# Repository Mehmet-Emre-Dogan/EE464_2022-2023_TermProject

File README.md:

# EE464_2022-2023_TermProject
 Hardware Project for EE464

 https://github.com/odtu/ee464

# Magnetic Design Report
 https://github.com/Mehmet-Emre-Dogan/EE464_2023_HW2_Team08
 
 # Experiments
 
 ## 0th Experiment
 https://youtu.be/MJ3PV6YCNdQ

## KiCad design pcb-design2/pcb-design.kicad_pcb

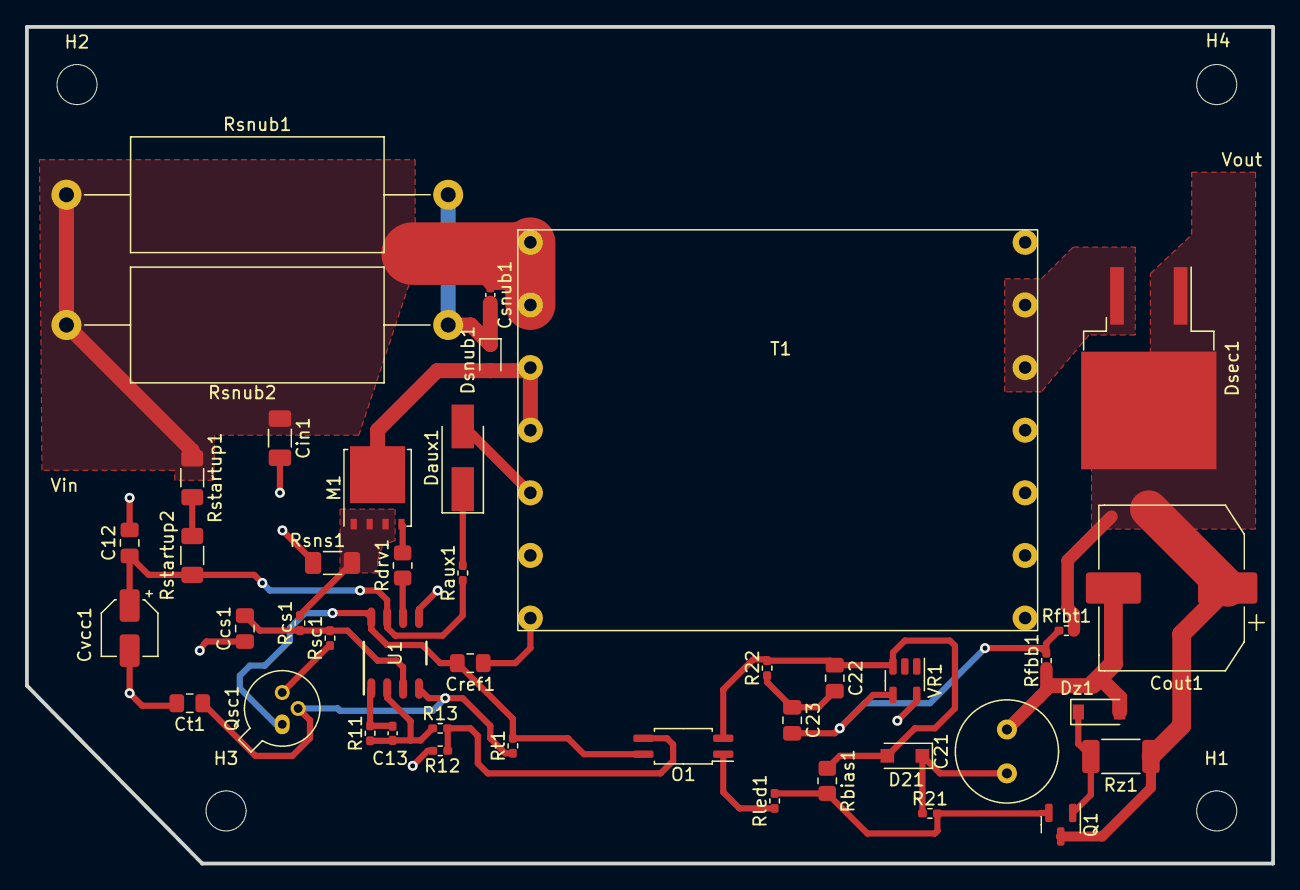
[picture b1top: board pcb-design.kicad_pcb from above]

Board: 2 copper layers, 99.5 x 66.8 mm, 48 parts (0 on the bottom side), 28 nets.

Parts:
C12: 100 nF; C_0805_2012Metric_Pad1.18x1.45mm_HandSolder
C13: 1 nF; C_0402_1005Metric_Pad0.74x0.62mm_HandSolder
C21: 68 uF; C_Radial_D8.0mm_H11.5mm_P3.50mm
C22: 22 pF; C_0805_2012Metric_Pad1.18x1.45mm_HandSolder
C23: 56 pF; C_0805_2012Metric_Pad1.18x1.45mm_HandSolder
Ccs1: 470 pF; C_0805_2012Metric_Pad1.18x1.45mm_HandSolder
Cin1: 4.7 uF; C_1206_3216Metric_Pad1.33x1.80mm_HandSolder
Cout1: 47 uF; CP_Elec_12.5x13
Cref1: 100 nF; C_0805_2012Metric_Pad1.18x1.45mm_HandSolder
Csnub1: 2.2 uF; C_0402_1005Metric_Pad0.74x0.62mm_HandSolder
Ct1: 1 nF; C_0805_2012Metric_Pad1.18x1.45mm_HandSolder
Cvcc1: 4.7 uF; CP_Elec_4x5.3
D21: PMEG6010CEH; D_SOD-123F
Daux1: D_Schottky; D_SMA_Handsoldering
Dsec1: D; TO-263-2_TabPin1
Dsnub1: D_Schottky; D_SOD-323
Dz1: D_Zener; D_SOD-123
H1, H2, H3, H4: MountingHole; MountingHole_3.2mm_M3
M1: CSD19502Q5B; TDSON-8-1
O1: TCMT1107; SOP-4_4.4x2.6mm_P1.27mm
Q1: BC846; SOT-23
Qsc1: 2N2646; TO-18-3
R11, R21: 10 kR; R_0402_1005Metric_Pad0.72x0.64mm_HandSolder
R12: 7.68 kR; R_0402_1005Metric_Pad0.72x0.64mm_HandSolder
R13: 4.99 kR; R_0402_1005Metric_Pad0.72x0.64mm_HandSolder
R22: 1.15 MR; R_0402_1005Metric_Pad0.72x0.64mm_HandSolder
Raux1: 10 R; R_0402_1005Metric_Pad0.72x0.64mm_HandSolder
Rbias1: 13.7 kR; R_0805_2012Metric_Pad1.20x1.40mm_HandSolder
Rcs1: 1 kR; R_0402_1005Metric_Pad0.72x0.64mm_HandSolder
Rdrv1: 12.1 R; R_0805_2012Metric_Pad1.20x1.40mm_HandSolder
Rfbb1: 3.01 kR; R_0402_1005Metric_Pad0.72x0.64mm_HandSolder
Rfbt1: 54.9 kR; R_0402_1005Metric_Pad0.72x0.64mm_HandSolder
Rled1: 16.2 kR; R_0402_1005Metric_Pad0.72x0.64mm_HandSolder
Rsc1: 4.32 kR; R_0402_1005Metric_Pad0.72x0.64mm_HandSolder
Rsns1: 33.9637 mR; R_1206_3216Metric_Pad1.30x1.75mm_HandSolder
Rsnub1, Rsnub2: 118.452 R; R_Axial_DIN0922_L20.0mm_D9.0mm_P30.48mm_Horizontal
Rstartup1, Rstartup2: 3.83 kR; R_1206_3216Metric_Pad1.30x1.75mm_HandSolder
Rt1: 7.5 kR; R_0402_1005Metric_Pad0.72x0.64mm_HandSolder
Rz1: 20 kR; R_2010_5025Metric_Pad1.40x2.65mm_HandSolder
T1: Transformer_1P_2S; Custom_Transformer-P0.5-7
U1: UCC2813D-1; UCC2813-1D
VR1: TL431DBV; SOT-23-5

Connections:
GND: C21.2, Cout1.2, Dz1.2 (A), Rfbb1.1, T1.11, T1.12, VR1.5 (A)
GNDREF: C12.2, Ccs1.1, Cin1.2, Cref1.1, Ct1.2, Cvcc1.2, R12.1, Rsns1.1, T1.6 (SD), T1.7, U1.5 (GND)
unnamed: C12.1, Cvcc1.1, Raux1.1, Rstartup2.2, U1.7 (VCC)
unnamed: C13.1, R11.1, R13.1, U1.2 (FB)
unnamed: C13.2, R11.2, U1.1 (COMP)
unnamed: C21.1, D21.1 (K), R21.1
unnamed: C22.1, D21.2 (A), O1.2, R22.2, Rbias1.1, VR1.3 (K)
unnamed: C22.2, C23.1, R22.1
unnamed: C23.2, Rfbb1.2, Rfbt1.1, VR1.4 (REF)
unnamed: Ccs1.2, Rcs1.1, Rsc1.2, U1.3 (CS)
unnamed: Cref1.2, O1.4, Qsc1.1 (B2), Rt1.2, U1.8 (REF)
unnamed: Csnub1.2, Dsnub1.1 (K), Rsnub1.2, Rsnub2.2
unnamed: Ct1.1, Qsc1.2 (E), Rt1.1, U1.4 (RC)
unnamed: Daux1.1 (K), Raux1.2
unnamed: Daux1.2 (A), T1.5 (SC)
unnamed: Dsec1.2 (A), T1.9, T1.10
unnamed: Dsnub1.2 (A), M1.5 (D), T1.3 (SA), T1.4 (SB)
unnamed: Dz1.1 (K), Q1.1 (B), Rz1.2
unnamed: M1.1 (S), M1.2 (S), M1.3 (S), Rcs1.2, Rsns1.2
unnamed: M1.4 (G), Rdrv1.2
unnamed: O1.1, Rled1.1
unnamed: O1.3, R12.2, R13.2
unnamed: Q1.2 (E), R21.2, Rbias1.2, Rled1.2
unnamed: Qsc1.3 (B1), Rsc1.1
unnamed: Rdrv1.1, U1.6 (OUT)
unnamed: Rstartup1.2, Rstartup2.1
VDC: Cin1.1, Csnub1.1, Rsnub1.1, Rsnub2.1, Rstartup1.1, T1.1 (AA), T1.2 (AB)
Vout: Cout1.1, Dsec1.1 (K), Q1.3 (C), Rfbt1.2, Rz1.1

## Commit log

2023-02-04 worked on fixed duty pwm generator
    used ne555
2023-02-04 added irfz44n to spice sim.
2023-02-05 redesign circuit with existing elements
2023-02-05 add experimental images for the 555 cct
2023-03-12 Create handdrawn_sch.jpeg
    an approach to perform DC isolation
2023-04-02 move files
2023-05-01 transformer winding experiment
2023-05-05 web scraper for part links
2023-05-06 BOM list updated.
2023-05-07 Create presentation.pptx
    - Problem Definition
    - Topology Selection
    - Plan B
    - Targeted Bonuses
2023-05-09 Presentation completed.
2023-05-11 Update README.md
    Add zeroth experiment video link
2023-05-21 copy core calculator mlx from the hw2
2023-05-21 turns calculation with a new core
2023-05-27 add skin depth calculation and
    recalculate the effective AC resistances
2023-06-11 Schematic and footprints added for PCB design.
2023-06-11 Transformer footprint is added.
2023-06-14 Schematic is corrected. PCB Design is added.
2023-06-14 Case design is added and some minor fixes on PCB design.
2023-06-14 pcb improvements
    - zones changed solid fill from thermal relief
    - thicken lines
    - add more zones
2023-06-21 Parts need update were marked for final report.
2023-06-27 overview the magnetic design
2023-06-27 update transformer section with new transformer
2023-06-27 pcb design dection added
2023-06-27 rewrite conclusion
    - compile calc.mlx to pdf
    - add appendices to be merged
2023-06-27 Final adjustments on report are done and pdf files are merged.
